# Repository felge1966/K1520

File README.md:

# K1520
Baugruppen für das K1520-System 

Baumass der Baugruppen i.d.R 170mm*95mm, womit sie in die "alten" EGS Systemgehäuse eingesetzt werden können.

Realisiert sind bisher:
- GIDE Interface mit 74HCT646 und DOM-IDE Schnittstelle
- USB Modul mit VDIP2 Modul 

Zur Adressfestlegung werden in den meisten Fällen GAL's verwendet.

weitere Baugruppen sind im Y23VO Verzeichnis (M.Kramer Mikrocomputer) zu finden.
https://github.com/felge1966/Y23vo

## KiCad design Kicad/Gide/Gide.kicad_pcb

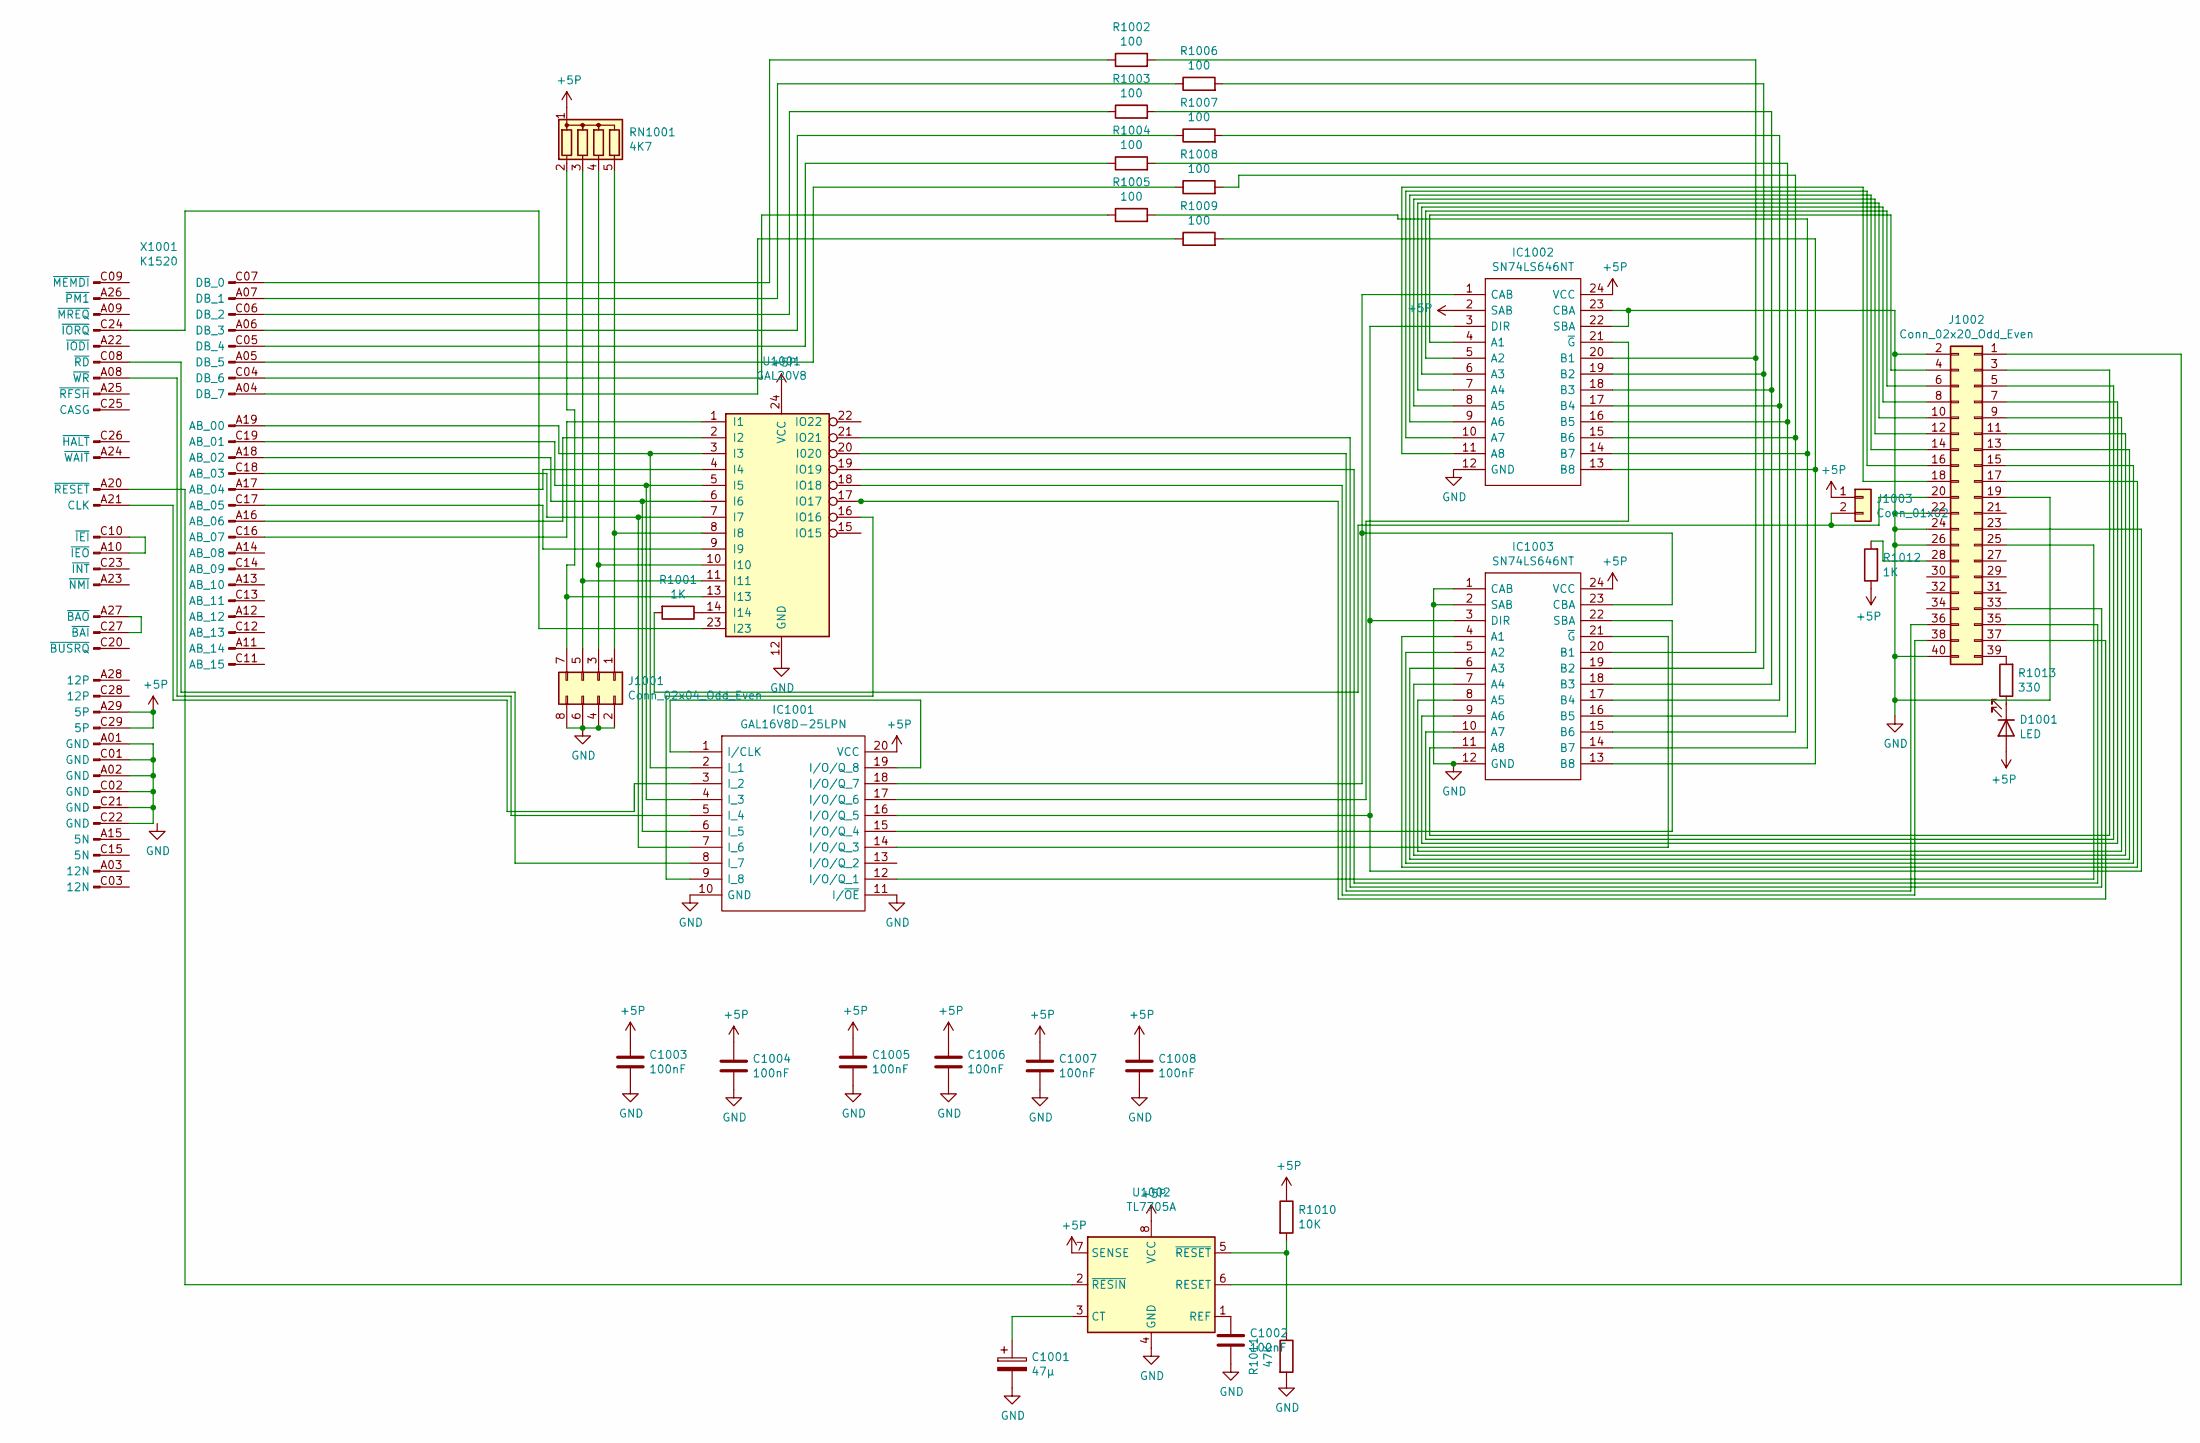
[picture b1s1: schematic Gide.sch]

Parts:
C1001: 47µ; CP_Radial_D4.0mm_P2.00mm
C1002, C1003, C1004, C1005, C1006, C1007, C1008: 100nF; C_Disc_D3.0mm_W1.6mm_P2.50mm
D1001: LED; LED_D3.0mm
IC1001: GAL16V8D-25LPN; DIP-20_W7.62mm_LongPads; Manufacturer_Part_Number GAL16V8D-25LPN; Mouser Part Number 842-GAL16V8D25LPN
IC1002, IC1003: SN74LS646NT; DIP-24_W15.24mm_LongPads; Manufacturer_Part_Number SN74LS646NT
J1001: Conn_02x04_Odd_Even; PinHeader_2x04_P2.54mm_Vertical
J1002: Conn_02x20_Odd_Even; PinHeader_2x20_P2.54mm_Horizontal
J1003: Conn_01x02; PinHeader_1x02_P2.54mm_Vertical
R1001, R1012: 1K; R_Axial_DIN0207_L6.3mm_D2.5mm_P10.16mm_Horizontal
R1002, R1003, R1004, R1005, R1006, R1007, R1008, R1009: 100; R_Axial_DIN0207_L6.3mm_D2.5mm_P10.16mm_Horizontal
R1010: 10K; R_Axial_DIN0207_L6.3mm_D2.5mm_P10.16mm_Horizontal
R1011: 47K; R_Axial_DIN0207_L6.3mm_D2.5mm_P10.16mm_Horizontal
R1013: 330; R_Axial_DIN0207_L6.3mm_D2.5mm_P10.16mm_Horizontal
RN1001: 4K7; R_Array_SIP5
U1001: GAL20V8; DIP-24_W7.62mm_LongPads
U1002: TL7705A; DIP-8_W7.62mm_LongPads
X1001: K1520; EFS2x29_DIN_male

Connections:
+5P: C1003.1, C1004.1, C1005.1, C1006.1, C1007.1, C1008.1, D1001.2 (A), IC1001.20 (VCC), IC1002.2 (SAB), IC1002.24 (VCC), IC1003.24 (VCC), J1003.1, R1010.1, R1012.1, RN1001.1 (common), U1001.24 (VCC), U1002.7 (SENSE), U1002.8 (VCC), X1001.A29 (5P), X1001.C29 (5P)
GND: C1001.2, C1002.2, C1003.2, C1004.2, C1005.2, C1006.2, C1007.2, C1008.2, IC1001.10 (GND), IC1001.11 (I/~OE), IC1002.12 (GND), IC1002.22 (SBA), IC1002.23 (CBA), IC1003.1 (CAB), IC1003.2 (SAB), IC1003.12 (GND), J1001.2, J1001.4, J1001.6, J1001.8, J1002.2, J1002.19, J1002.22, J1002.24, J1002.26, J1002.40, R1011.2, U1001.12 (GND), U1002.4 (GND)
unnamed: C1001.1, U1002.3 (CT)
unnamed: C1002.1, U1002.1 (REF)
unnamed: D1001.1 (K), R1013.1
unnamed: IC1001.1 (I/CLK), IC1001.19 (I/O/Q_8)
unnamed: IC1001.2 (I_1), U1001.3 (I3), X1001.A19 (AB_00)
unnamed: IC1001.3 (I_2), X1001.A21 (CLK)
unnamed: IC1001.4 (I_3), U1001.5 (I5), X1001.C19 (AB_01)
unnamed: IC1001.5 (I_4), X1001.A08 (~WR)
unnamed: IC1001.6 (I_5), U1001.6 (I6), X1001.A18 (AB_02)
unnamed: IC1001.7 (I_6), U1001.7 (I7), X1001.C18 (AB_03)
unnamed: IC1001.8 (I_7), X1001.C08 (~RD)
unnamed: IC1001.9 (I_8), U1001.16 (IO16)
unnamed: IC1001.12 (I/O/Q_1), J1002.25
unnamed: IC1001.14 (I/O/Q_3), IC1003.21 (~G)
unnamed: IC1001.15 (I/O/Q_4), IC1003.22 (SBA)
unnamed: IC1001.16 (I/O/Q_5), IC1002.3 (DIR), IC1003.3 (DIR), J1002.23
unnamed: IC1001.17 (I/O/Q_6), IC1002.21 (~G)
unnamed: IC1001.18 (I/O/Q_7), IC1002.1 (CAB), IC1003.23 (CBA)
unnamed: IC1002.4 (A1), J1002.4
unnamed: IC1002.5 (A2), J1002.6
unnamed: IC1002.6 (A3), J1002.8
unnamed: IC1002.7 (A4), J1002.10
unnamed: IC1002.8 (A5), J1002.12
unnamed: IC1002.9 (A6), J1002.14
unnamed: IC1002.10 (A7), J1002.16
unnamed: IC1002.11 (A8), J1002.18
unnamed: IC1002.13 (B8), IC1003.13 (B8), R1009.2
unnamed: IC1002.14 (B7), IC1003.14 (B7), R1005.2
unnamed: IC1002.15 (B6), IC1003.15 (B6), R1008.2
unnamed: IC1002.16 (B5), IC1003.16 (B5), R1004.2
unnamed: IC1002.17 (B4), IC1003.17 (B4), R1007.2
unnamed: IC1002.18 (B3), IC1003.18 (B3), R1003.2
unnamed: IC1002.19 (B2), IC1003.19 (B2), R1006.2
unnamed: IC1002.20 (B1), IC1003.20 (B1), R1002.2
unnamed: IC1003.4 (A1), J1002.17
unnamed: IC1003.5 (A2), J1002.15
unnamed: IC1003.6 (A3), J1002.13
unnamed: IC1003.7 (A4), J1002.11
unnamed: IC1003.8 (A5), J1002.9
unnamed: IC1003.9 (A6), J1002.7
unnamed: IC1003.10 (A7), J1002.5
unnamed: IC1003.11 (A8), J1002.3
unnamed: J1001.1, RN1001.5 (R4), U1001.8 (I8)
unnamed: J1001.3, RN1001.4 (R3), U1001.10 (I10)
unnamed: J1001.5, RN1001.3 (R2), U1001.11 (I11)
unnamed: J1001.7, RN1001.2 (R1), U1001.13 (I13)
unnamed: J1002.1, U1002.6 (RESET)
unnamed: J1002.20, J1003.2, R1001.2
unnamed: J1002.28, R1012.2
unnamed: J1002.33, U1001.21 (IO21)
unnamed: J1002.35, U1001.19 (IO19)
unnamed: J1002.36, U1001.20 (I020)
unnamed: J1002.37, U1001.17 (IO17)
unnamed: J1002.38, U1001.18 (IO18)
unnamed: J1002.39, R1013.2
unnamed: R1001.1, U1001.14 (I14)
unnamed: R1002.1, X1001.C07 (DB_0)
unnamed: R1003.1, X1001.C06 (DB_2)
unnamed: R1004.1, X1001.C05 (DB_4)
unnamed: R1005.1, X1001.C04 (DB_6)
unnamed: R1006.1, X1001.A07 (DB_1)
unnamed: R1007.1, X1001.A06 (DB_3)
unnamed: R1008.1, X1001.A05 (DB_5)
unnamed: R1009.1, X1001.A04 (DB_7)
unnamed: R1010.2, R1011.1, U1002.5 (~RESET)
unnamed: U1001.1 (I1), X1001.C16 (AB_07)
unnamed: U1001.2 (I2), X1001.A16 (AB_06)
unnamed: U1001.4 (I4), X1001.A17 (AB_04)
unnamed: U1001.9 (I9), X1001.C17 (AB_05)
unnamed: U1001.23 (I23), X1001.C24 (~IORQ)
unnamed: U1002.2 (~RESIN), X1001.A20 (~RESET)
unnamed: X1001.A01 (GND), X1001.A02 (GND), X1001.C01 (GND), X1001.C02 (GND), X1001.C21 (GND), X1001.C22 (GND)
unnamed: X1001.A10 (~IEO), X1001.C10 (~IEI)
unnamed: X1001.A27 (~BAO), X1001.C27 (~BAI)

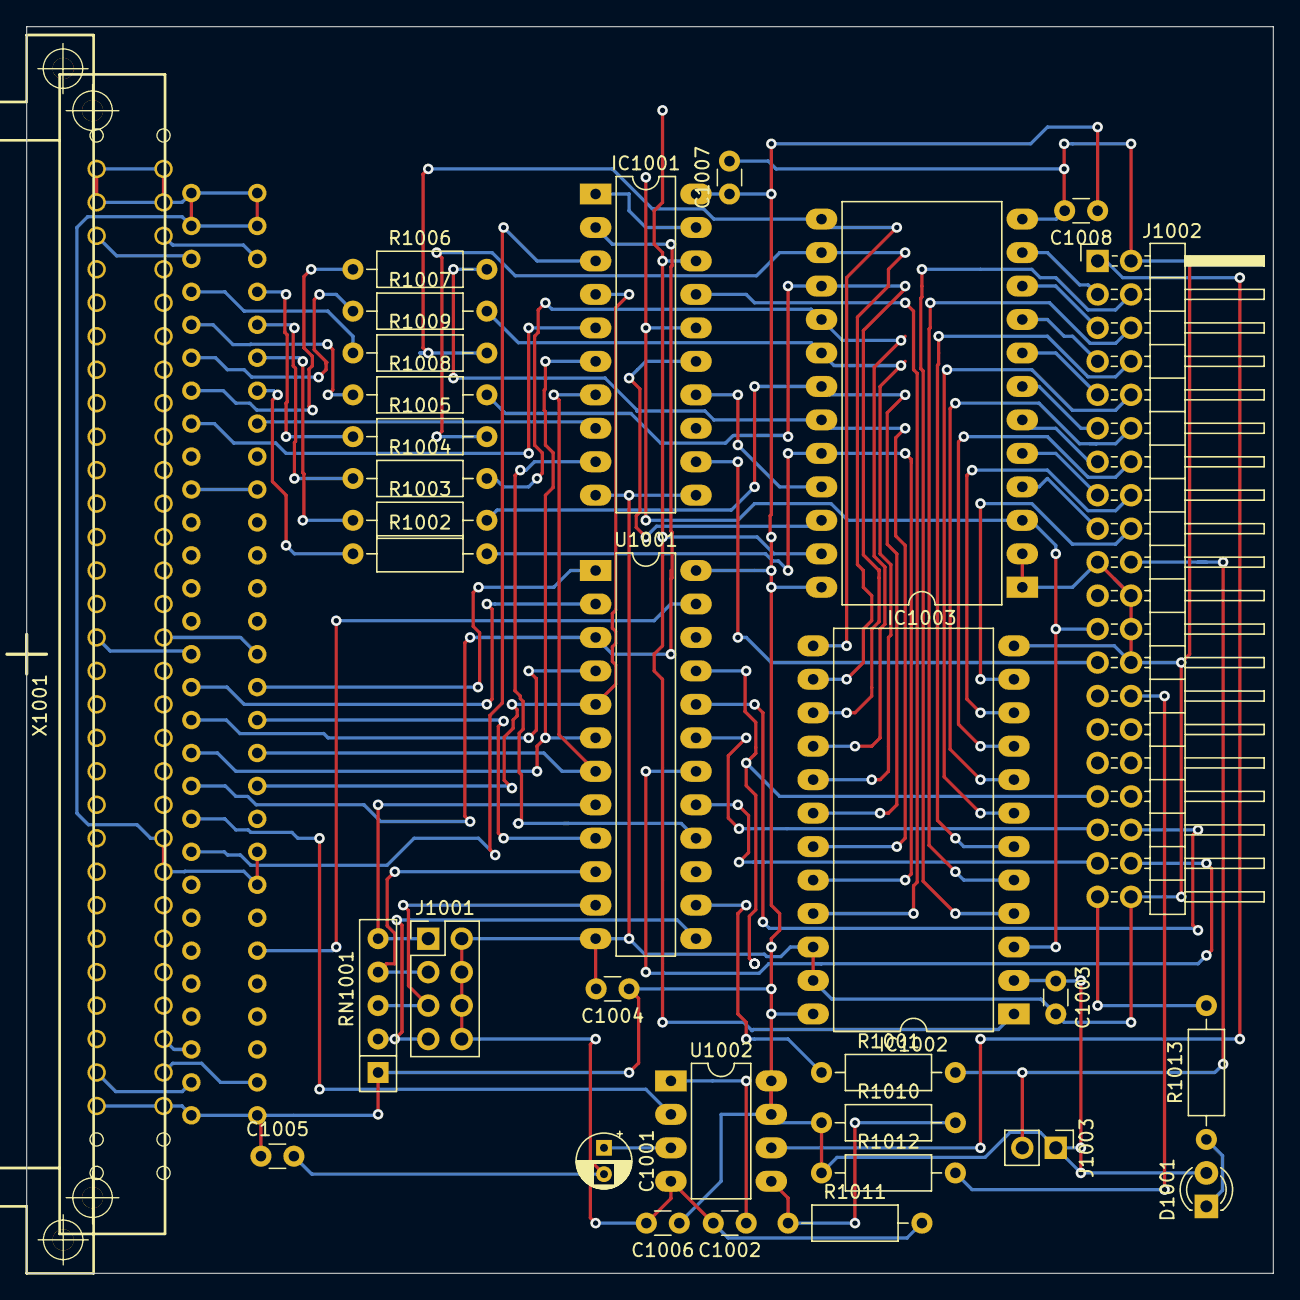
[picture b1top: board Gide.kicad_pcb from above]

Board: 2 copper layers, 94.6 x 94.6 mm, 32 parts (0 on the bottom side), 76 nets.

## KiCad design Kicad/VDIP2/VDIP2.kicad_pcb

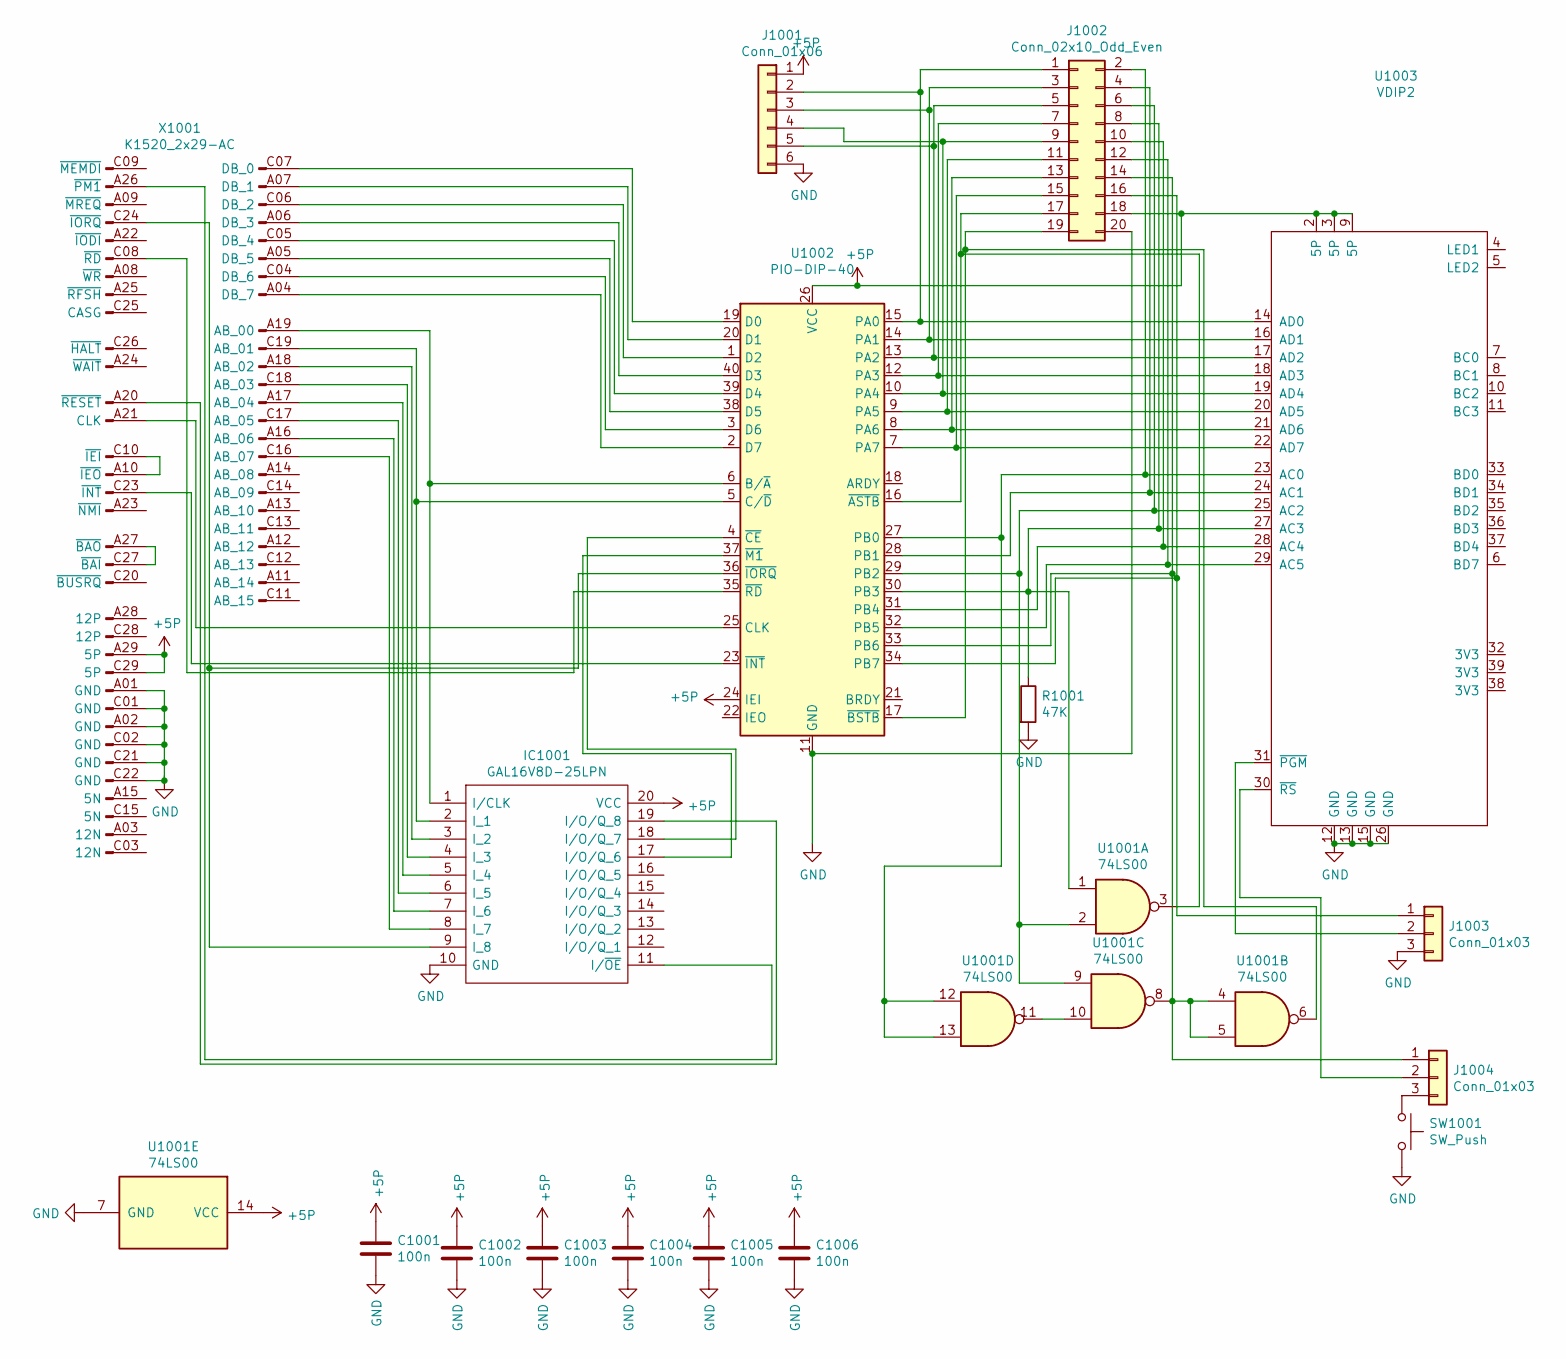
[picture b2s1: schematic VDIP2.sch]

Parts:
C1001, C1002, C1003, C1004, C1005, C1006: 100n; C_Disc_D3.0mm_W1.6mm_P2.50mm
IC1001: GAL16V8D-25LPN; DIP-20_W7.62mm_LongPads; Manufacturer_Part_Number GAL16V8D-25LPN; Mouser Part Number 842-GAL16V8D25LPN
J1001: Conn_01x06; PinHeader_1x06_P2.54mm_Vertical
J1002: Conn_02x10_Odd_Even; PinHeader_2x10_P2.54mm_Vertical
J1003, J1004: Conn_01x03; PinHeader_1x03_P2.54mm_Vertical
R1001: 47K; R_Axial_DIN0207_L6.3mm_D2.5mm_P10.16mm_Horizontal
SW1001: SW_Push; SW_PUSH_6mm_H4.3mm
U1001: 74LS00; DIP-14_W7.62mm_LongPads
U1002: PIO-DIP-40; DIP-40_W15.24mm
U1003: VDIP2; DIP-40_W15.24mm_LongPads
X1001: K1520_2x29-AC; K1520_EFS2x29_DIN_male

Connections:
+5P: C1001.1, C1002.1, C1003.1, C1004.1, C1005.1, C1006.1, IC1001.20 (VCC), J1001.1, J1002.18, U1001.14 (VCC), U1002.24 (IEI), U1002.26 (VCC), U1003.2 (5P), U1003.3 (5P), U1003.9 (5P), X1001.A29 (5P), X1001.C29 (5P)
GND: C1001.2, C1002.2, C1003.2, C1004.2, C1005.2, C1006.2, IC1001.10 (GND), J1001.6, J1002.20, J1003.3, R1001.2, SW1001.2, U1001.7 (GND), U1002.11 (GND), U1003.12 (GND), U1003.13 (GND), U1003.15 (GND), U1003.26 (GND), X1001.A01 (GND), X1001.A02 (GND), X1001.C01 (GND), X1001.C02 (GND), X1001.C21 (GND), X1001.C22 (GND)
unnamed: IC1001.1 (I/CLK), U1002.6 (B/~A~), X1001.A19 (AB_00)
unnamed: IC1001.2 (I_1), U1002.5 (C/~D~), X1001.C19 (AB_01)
unnamed: IC1001.3 (I_2), X1001.A18 (AB_02)
unnamed: IC1001.4 (I_3), X1001.C18 (AB_03)
unnamed: IC1001.5 (I_4), X1001.A17 (AB_04)
unnamed: IC1001.6 (I_5), X1001.C17 (AB_05)
unnamed: IC1001.7 (I_6), X1001.A16 (AB_06)
unnamed: IC1001.8 (I_7), X1001.C16 (AB_07)
unnamed: IC1001.9 (I_8), U1002.36 (~IORQ~), X1001.C24 (~IORQ)
unnamed: IC1001.11 (I/~OE), X1001.A26 (~PM1)
unnamed: IC1001.17 (I/O/Q_6), U1002.37 (~M1~)
unnamed: IC1001.18 (I/O/Q_7), U1002.4 (~CE~)
unnamed: IC1001.19 (I/O/Q_8), X1001.A20 (~RESET)
unnamed: J1001.2, J1002.1, U1002.15 (PA0), U1003.14 (AD0)
unnamed: J1001.3, J1002.3, U1002.14 (PA1), U1003.16 (AD1)
unnamed: J1001.4, J1002.9, U1002.10 (PA4), U1003.19 (AD4)
unnamed: J1001.5, J1002.5, U1002.13 (PA2), U1003.17 (AD2)
unnamed: J1002.2, U1001.12, U1001.13, U1002.27 (PB0), U1003.23 (AC0)
unnamed: J1002.4, U1002.28 (PB1), U1003.24 (AC1)
unnamed: J1002.6, U1001.2, U1001.9, U1002.29 (PB2), U1003.25 (AC2)
unnamed: J1002.7, U1002.12 (PA3), U1003.18 (AD3)
unnamed: J1002.8, R1001.1, U1001.1, U1002.30 (PB3), U1003.27 (AC3)
unnamed: J1002.10, U1002.31 (PB4), U1003.28 (AC4)
unnamed: J1002.11, U1002.9 (PA5), U1003.20 (AD5)
unnamed: J1002.12, U1002.32 (PB5), U1003.29 (AC5)
unnamed: J1002.13, U1002.8 (PA6), U1003.21 (AD6)
unnamed: J1002.14, J1004.1, U1001.4, U1001.5, U1001.8, U1002.33 (PB6)
unnamed: J1002.15, U1002.7 (PA7), U1003.22 (AD7)
unnamed: J1002.16, J1003.1, U1002.34 (PB7)
unnamed: J1002.17, U1001.3, U1002.16 (~ASTB~)
unnamed: J1002.19, U1001.6, U1002.17 (~BSTB~)
unnamed: J1003.2, U1003.31 (~PGM)
unnamed: J1004.2, U1003.30 (~RS)
unnamed: J1004.3, SW1001.1
unnamed: U1001.10, U1001.11
unnamed: U1002.1 (D2), X1001.C06 (DB_2)
unnamed: U1002.2 (D7), X1001.A04 (DB_7)
unnamed: U1002.3 (D6), X1001.C04 (DB_6)
unnamed: U1002.19 (D0), X1001.C07 (DB_0)
unnamed: U1002.20 (D1), X1001.A07 (DB_1)
unnamed: U1002.23 (~INT~), X1001.C23 (~INT)
unnamed: U1002.25 (CLK), X1001.A21 (CLK)
unnamed: U1002.35 (~RD~), X1001.C08 (~RD)
unnamed: U1002.38 (D5), X1001.A05 (DB_5)
unnamed: U1002.39 (D4), X1001.C05 (DB_4)
unnamed: U1002.40 (D3), X1001.A06 (DB_3)
unnamed: X1001.A10 (~IEO), X1001.C10 (~IEI)
unnamed: X1001.A27 (~BAO), X1001.C27 (~BAI)

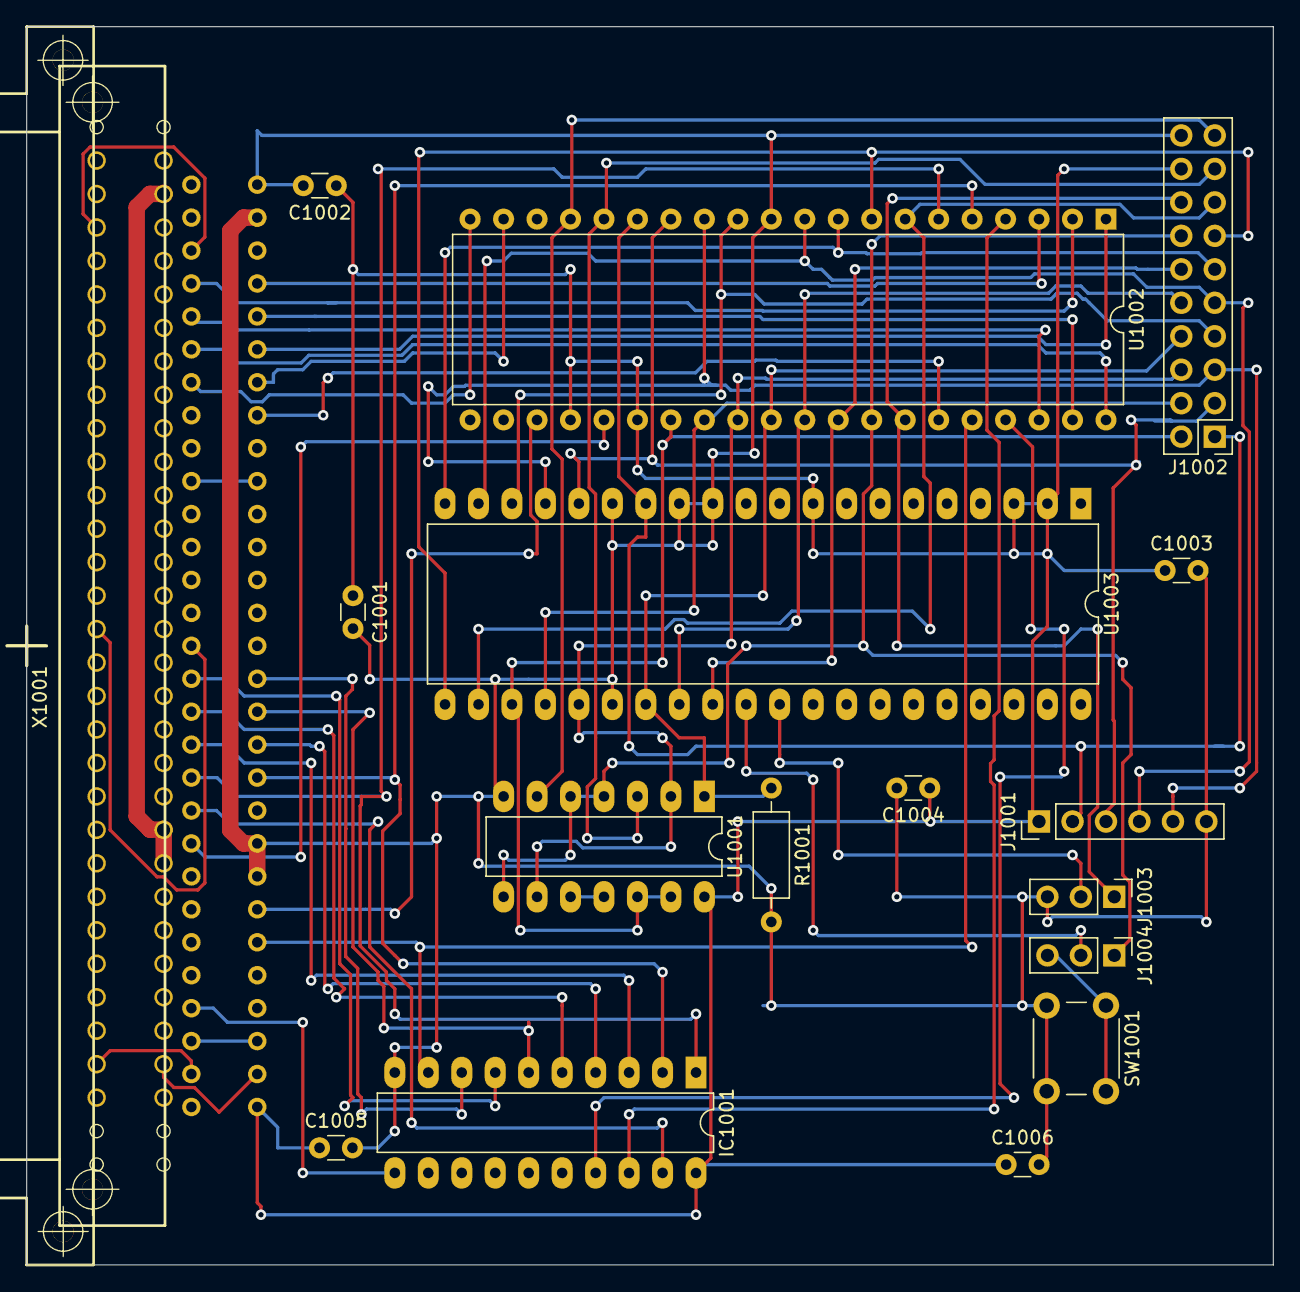
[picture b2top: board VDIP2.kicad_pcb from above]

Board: 2 copper layers, 94.6 x 94.0 mm, 17 parts (0 on the bottom side), 50 nets.
